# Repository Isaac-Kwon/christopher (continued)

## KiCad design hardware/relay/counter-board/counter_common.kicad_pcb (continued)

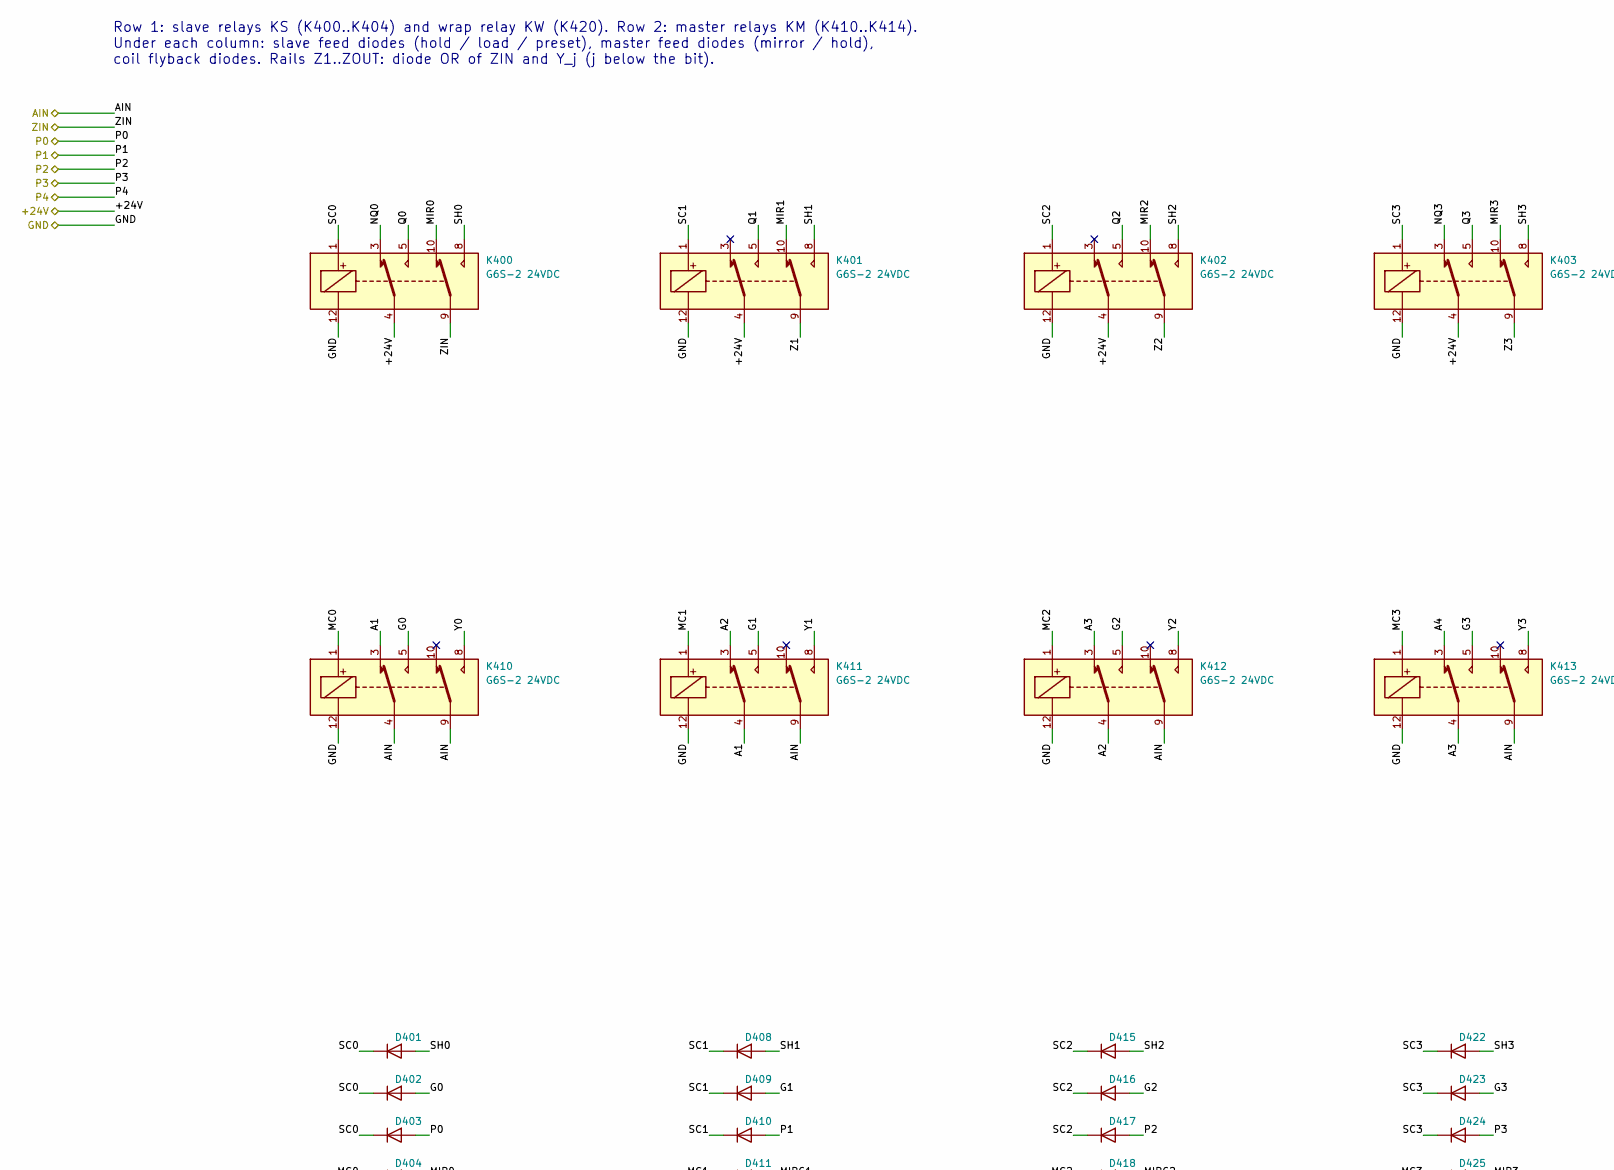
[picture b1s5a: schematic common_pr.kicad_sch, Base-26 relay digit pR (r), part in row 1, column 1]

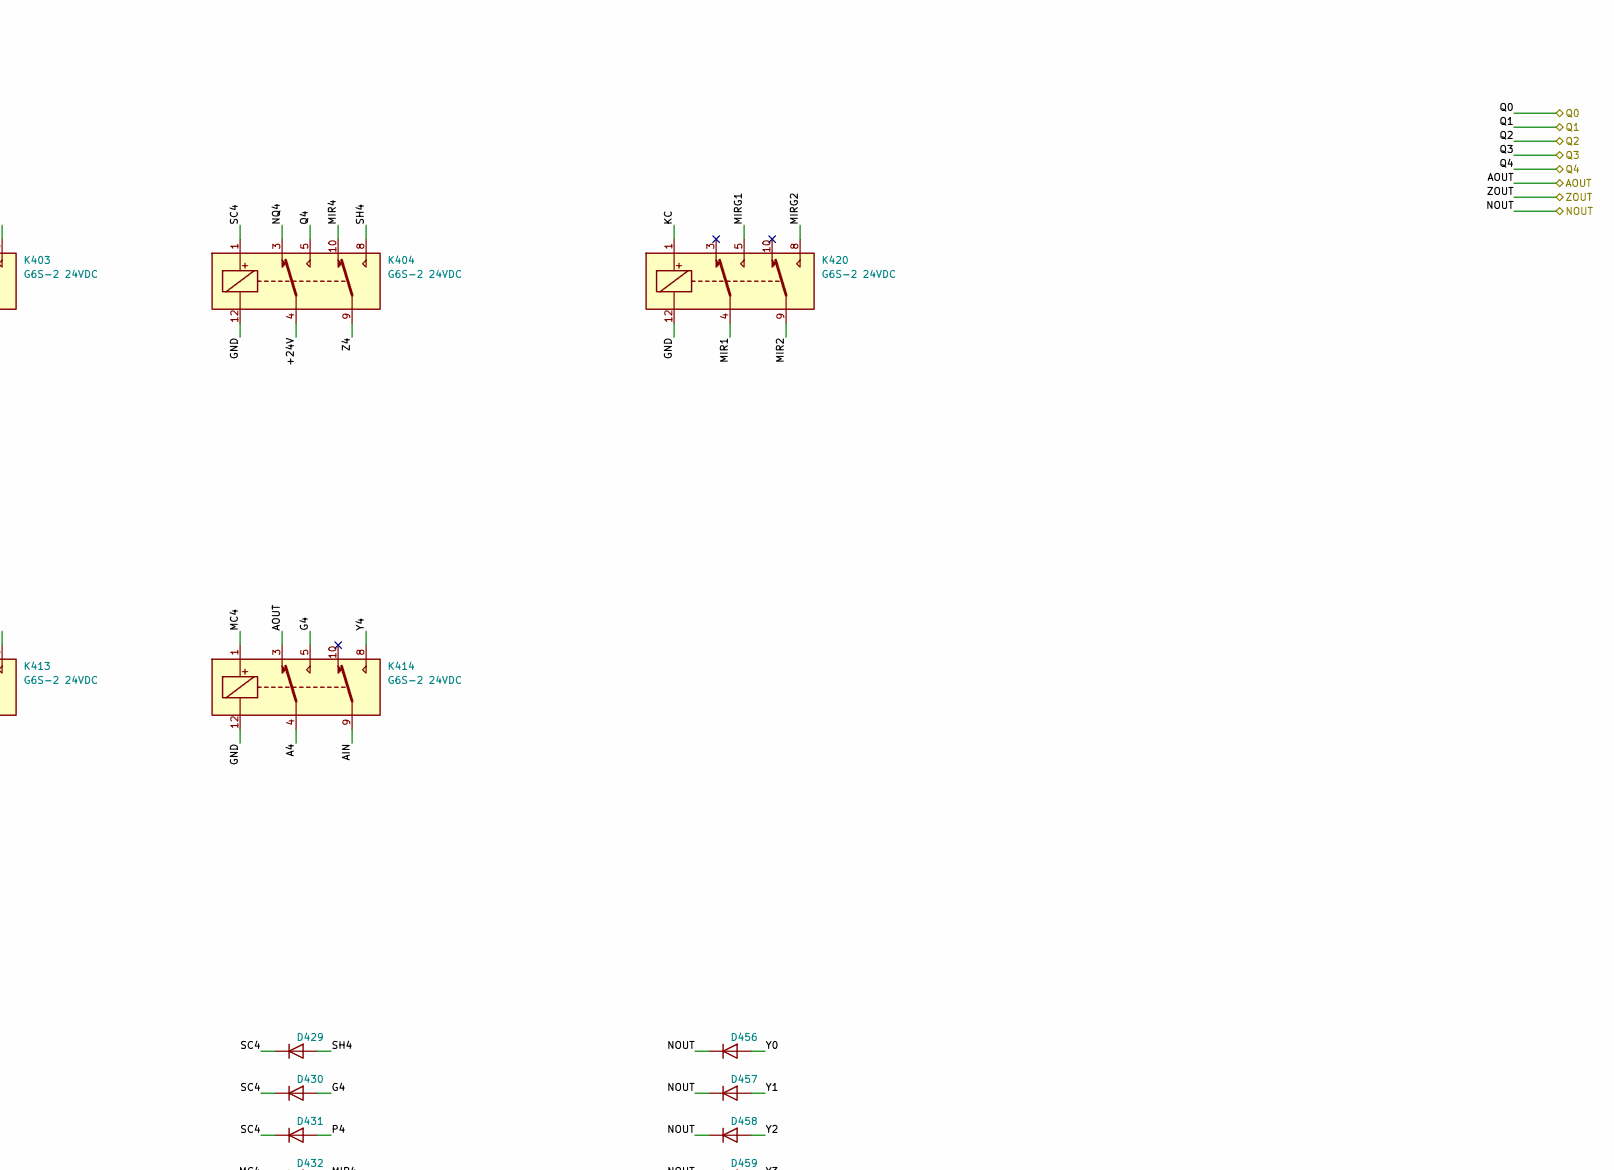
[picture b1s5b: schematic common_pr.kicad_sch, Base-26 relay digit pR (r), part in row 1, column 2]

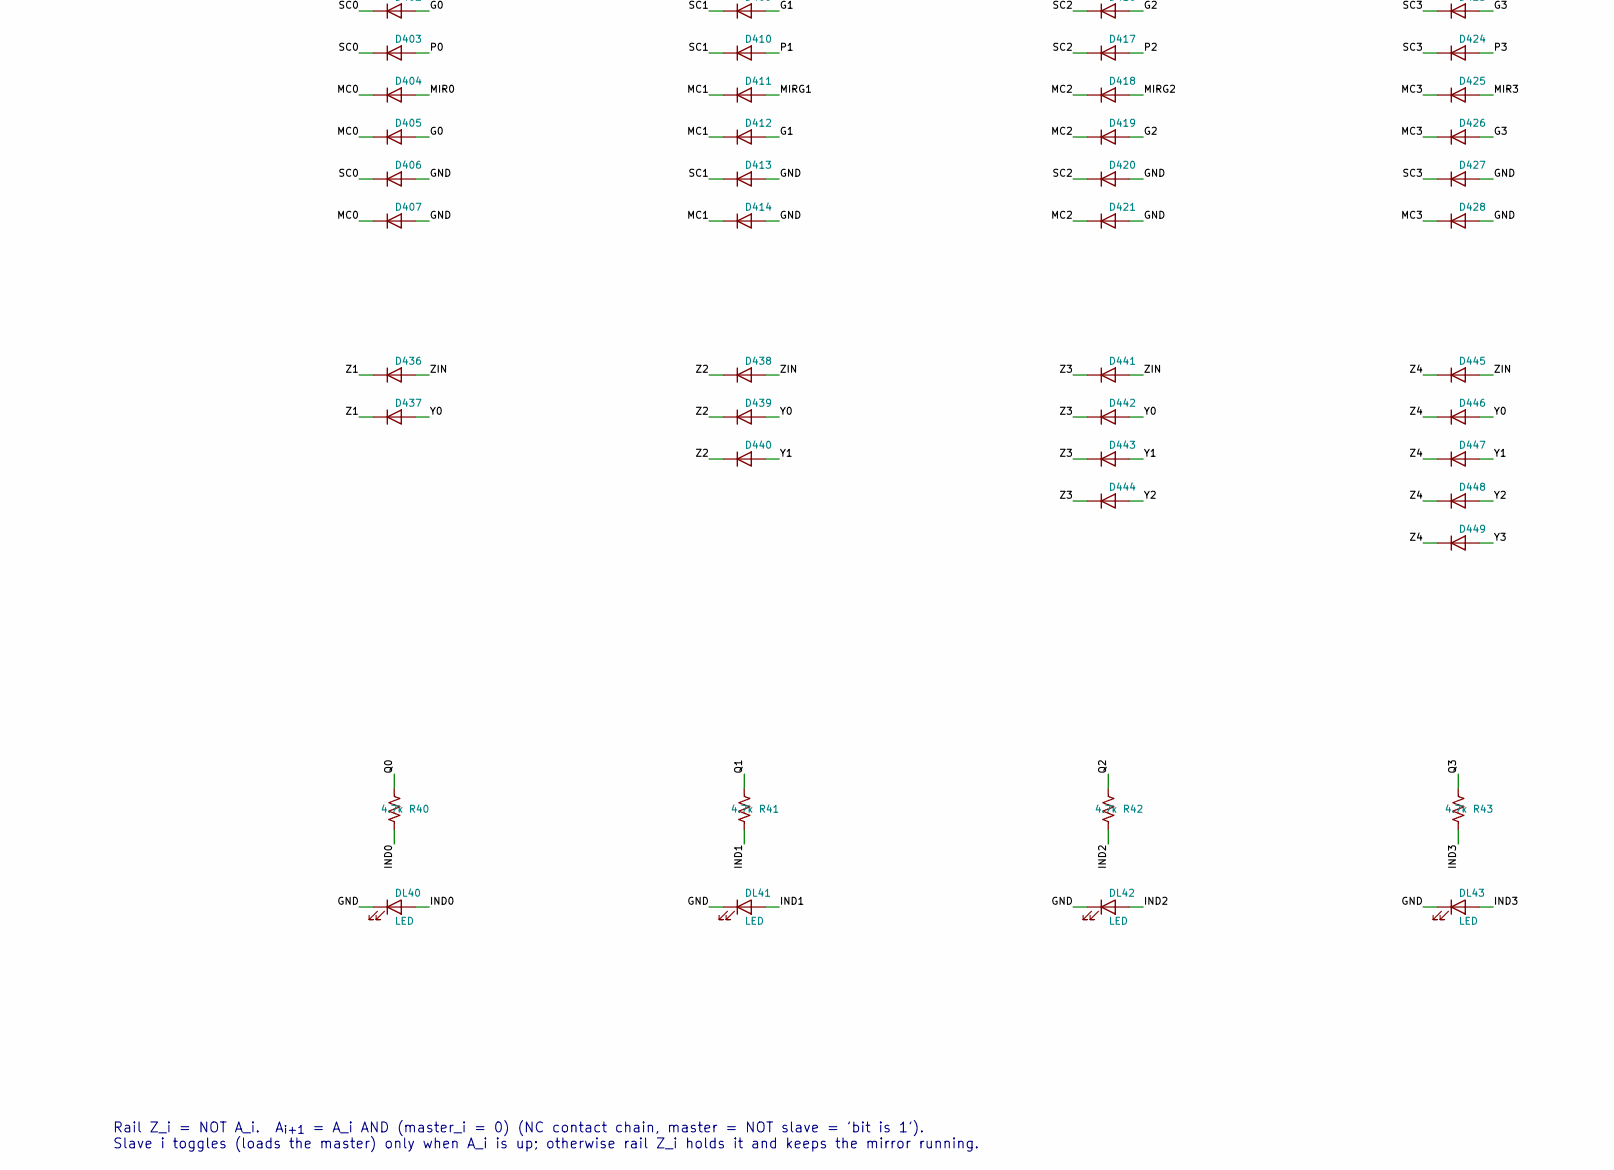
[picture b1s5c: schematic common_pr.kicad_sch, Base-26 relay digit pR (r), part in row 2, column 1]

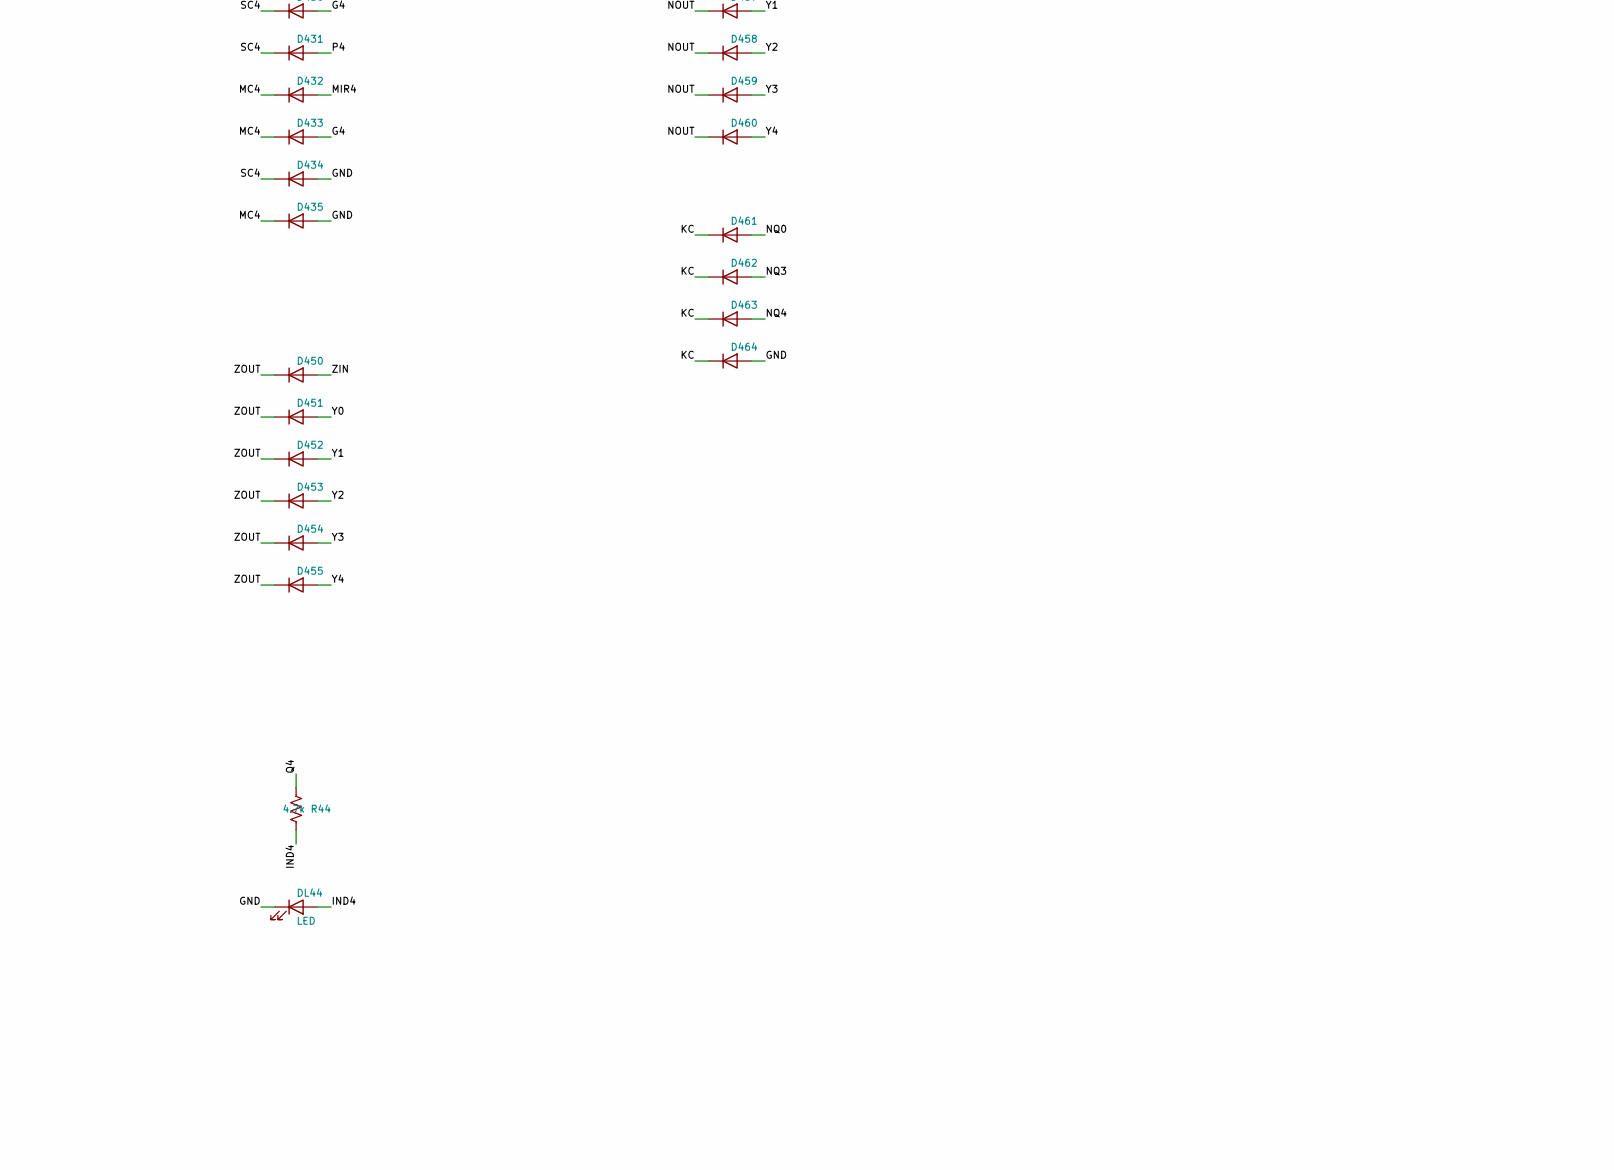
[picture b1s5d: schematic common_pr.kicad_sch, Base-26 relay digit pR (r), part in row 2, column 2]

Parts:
D401, D402, D403, D404, D405, D408, D409, D410, D411, D412, D415, D416, D417, D418, D419, D422, D423, D424, D425, D426, D429, D430, D431, D432, D433, D436, D437, D438, D439, D440, D441, D442, D443, D444, D445, D446, D447, D448, D449, D450, D451, D452, D453, D454, D455, D456, D457, D458, D459, D460, D461, D462, D463: 1N5819W; D_SOD-123
D406, D407, D413, D414, D420, D421, D427, D428, D434, D435, D464: 1N4148W; D_SOD-123
DL40, DL41, DL42, DL43, DL44: LED; LED_0603_1608Metric
K400, K401, K402, K403, K404, K410, K411, K412, K413, K414, K420: G6S-2 24VDC; Relay_DPDT_Omron_G6S-2
R40, R41, R42, R43, R44: 4.7k; R_0603_1608Metric

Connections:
/+24V: K400.4, K401.4, K402.4, K403.4, K404.4; also elsewhere on the board
/A1B: K410.4, K410.9, K411.9, K412.9, K413.9, K414.9; also elsewhere on the board
/DIGIT_PR/A1: K410.3, K411.4
/DIGIT_PR/A2: K411.3, K412.4
/DIGIT_PR/A3: K412.3, K413.4
/DIGIT_PR/A4: K413.3, K414.4
/DIGIT_PR/AOUT: K414.3
/DIGIT_PR/G0: D402.2 (A), D405.2 (A), K410.5
/DIGIT_PR/G1: D409.2 (A), D412.2 (A), K411.5
/DIGIT_PR/G2: D416.2 (A), D419.2 (A), K412.5
/DIGIT_PR/G3: D423.2 (A), D426.2 (A), K413.5
/DIGIT_PR/G4: D430.2 (A), D433.2 (A), K414.5
/DIGIT_PR/IND0: DL40.2 (A), R40.2
/DIGIT_PR/IND1: DL41.2 (A), R41.2
/DIGIT_PR/IND2: DL42.2 (A), R42.2
/DIGIT_PR/IND3: DL43.2 (A), R43.2
/DIGIT_PR/IND4: DL44.2 (A), R44.2
/DIGIT_PR/KC: D461.1 (K), D462.1 (K), D463.1 (K), D464.1 (K), K420.1
/DIGIT_PR/MC0: D404.1 (K), D405.1 (K), D407.1 (K), K410.1
/DIGIT_PR/MC1: D411.1 (K), D412.1 (K), D414.1 (K), K411.1
/DIGIT_PR/MC2: D418.1 (K), D419.1 (K), D421.1 (K), K412.1
/DIGIT_PR/MC3: D425.1 (K), D426.1 (K), D428.1 (K), K413.1
/DIGIT_PR/MC4: D432.1 (K), D433.1 (K), D435.1 (K), K414.1
/DIGIT_PR/MIR0: D404.2 (A), K400.10
/DIGIT_PR/MIR1: K401.10, K420.4
/DIGIT_PR/MIR2: K402.10, K420.9
/DIGIT_PR/MIR3: D425.2 (A), K403.10
/DIGIT_PR/MIR4: D432.2 (A), K404.10
/DIGIT_PR/MIRG1: D411.2 (A), K420.5
/DIGIT_PR/MIRG2: D418.2 (A), K420.8
/DIGIT_PR/NOUT: D456.1 (K), D457.1 (K), D458.1 (K), D459.1 (K), D460.1 (K)
/DIGIT_PR/NQ0: D461.2 (A), K400.3
/DIGIT_PR/NQ3: D462.2 (A), K403.3
/DIGIT_PR/NQ4: D463.2 (A), K404.3
/DIGIT_PR/SC0: D401.1 (K), D402.1 (K), D403.1 (K), D406.1 (K), K400.1
/DIGIT_PR/SC1: D408.1 (K), D409.1 (K), D410.1 (K), D413.1 (K), K401.1
/DIGIT_PR/SC2: D415.1 (K), D416.1 (K), D417.1 (K), D420.1 (K), K402.1
/DIGIT_PR/SC3: D422.1 (K), D423.1 (K), D424.1 (K), D427.1 (K), K403.1
/DIGIT_PR/SC4: D429.1 (K), D430.1 (K), D431.1 (K), D434.1 (K), K404.1
/DIGIT_PR/SH0: D401.2 (A), K400.8
/DIGIT_PR/SH1: D408.2 (A), K401.8
/DIGIT_PR/SH2: D415.2 (A), K402.8
/DIGIT_PR/SH3: D422.2 (A), K403.8
/DIGIT_PR/SH4: D429.2 (A), K404.8
/DIGIT_PR/Y0: D437.2 (A), D439.2 (A), D442.2 (A), D446.2 (A), D451.2 (A), D456.2 (A), K410.8
/DIGIT_PR/Y1: D440.2 (A), D443.2 (A), D447.2 (A), D452.2 (A), D457.2 (A), K411.8
/DIGIT_PR/Y2: D444.2 (A), D448.2 (A), D453.2 (A), D458.2 (A), K412.8
/DIGIT_PR/Y3: D449.2 (A), D454.2 (A), D459.2 (A), K413.8
/DIGIT_PR/Y4: D455.2 (A), D460.2 (A), K414.8
/DIGIT_PR/Z1: D436.1 (K), D437.1 (K), K401.9
/DIGIT_PR/Z2: D438.1 (K), D439.1 (K), D440.1 (K), K402.9
/DIGIT_PR/Z3: D441.1 (K), D442.1 (K), D443.1 (K), D444.1 (K), K403.9
/DIGIT_PR/Z4: D445.1 (K), D446.1 (K), D447.1 (K), D448.1 (K), D449.1 (K), K404.9
/DIGIT_PR/ZOUT: D450.1 (K), D451.1 (K), D452.1 (K), D453.1 (K), D454.1 (K), D455.1 (K)
/GND: D403.2 (A), D406.2 (A), D407.2 (A), D410.2 (A), D413.2 (A), D414.2 (A), D417.2 (A), D420.2 (A), D421.2 (A), D424.2 (A), D427.2 (A), D428.2 (A), D431.2 (A), D434.2 (A), D435.2 (A), D464.2 (A), DL40.1 (K), DL41.1 (K), DL42.1 (K), DL43.1 (K), DL44.1 (K), K400.12, K401.12, K402.12, K403.12, K404.12, K410.12, K411.12, K412.12, K413.12, K414.12, K420.12; also elsewhere on the board
/R0: K400.5, R40.1; also elsewhere on the board
/R1: K401.5, R41.1; also elsewhere on the board
/R2: K402.5, R42.1; also elsewhere on the board
/R3: K403.5, R43.1; also elsewhere on the board
/R4: K404.5, R44.1; also elsewhere on the board
/Z1B: D436.2 (A), D438.2 (A), D441.2 (A), D445.2 (A), D450.2 (A), K400.9; also elsewhere on the board

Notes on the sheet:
Row 1: slave relays KS (K400..K404) and wrap relay KW (K420). Row 2: master relays KM (K410..K414). Under each column: slave feed diodes (hold / load / preset), master feed diodes (mirror / hold), coil flyback diodes. Rails Z1..ZOUT: diode OR of ZIN and Y_j (j below the bit).
Rail Z_i = NOT A_i. A_{i+1} = A_i AND (master_i = 0) (NC contact chain, master = NOT slave = 'bit is 1'). Slave i toggles (loads the master) only when A_i is up; otherwise rail Z_i holds it and keeps the mirror running.

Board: 4 copper layers, 391 parts (0 on the bottom side), 264 nets, no tracks yet.

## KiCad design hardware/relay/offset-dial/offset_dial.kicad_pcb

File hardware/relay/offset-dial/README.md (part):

# 릴레이식 오프셋 다이얼과 다이얼 띠 (모듈 N, 회로도 + 기판 배치 + 기구 치수)

작성일: 2026-11-16 · 상태: **코드 트랙 회전 스위치(고정자 기판) 생성, ERC 0건, 기판 동박 형상 × 회전자 모델 × 계수기 유닛 보드 넷리스트로 26위치 전부 검증(허용 오차 모서리, break-before-make 훑기, 시스템 구동), 음성 시험 8/8(+ 기판 3/3), 기판 배치(미배선) DRC 0건, 배선은 사용자가. 기구(회전자·멈춤·손잡이)는 치수로만.** · 관련: `hardware/relay/layout.md` 3.5절(다이얼 띠), 5절 4번, `hardware/relay/concept.md` 5.2절, `hardware/relay/counter-board/README.md` 3·5절(유닛 J2 `DIAL`), `docs/decisions/0003-interfaces.md` 5.1–5.2절, `hardware/common/power-unit.md` 4절(전원 리셋 버튼), 기준 모델 `crates/christopher-core/src/relay.rs`(`Counters`), 메뉴 카드 `hardware/common/menu-cards/*.json`(`drum_offset_letters`)

**표기.** **(계산)** = 이 문서의 산술, **(추정)** = 실측·시제품 전 값, **(미확인)** = 데이터시트로 확인하지 못한 것. 단위는 mm, 각도는 관람객 쪽에서 본 시계 방향(12시 = 0°).

## 1. 무엇인가

유닛마다 하나씩 있는 **26위치 회전 스위치**다. 관람객(또는 운영자)이 메뉴 카드의 크립 오프셋 글자(`drum_offset_letters`의 셋째 글자, k = 글자 − A)에 손잡이를 맞추면, `HOME` 때 그 유닛의 계수기 유닛 보드가 a1 = k, a2 = −k mod 26을 프리셋으로 받는다(`counter-board/README.md` 3절, `relay.rs` `Counters::home`).

26위치 기성 회전 스위치는 찾지 못했다(`concept.md` 5.2절). 그래서 **기판 자체가 고정자**인 코드 트랙 스위치를 만들었다.

| 부분 | 내용 | 이 디렉터리에서 |
|---|---|---|
| 고정자 | 116 × 58 기판 한 장(2층). 회전자 쪽(F)에 동심 링 11개(COM + a1·a2 각 5비트), 관람객 쪽(B)에 글자 눈금 A–Z | 회로도·기판 배치(생성), 형상 검증 |
| 회전자 | 와이퍼 빗(끝 11개, 한 도체 = COM 다리), 허브 | 치수(4절, `dialmech.py`) |
| 멈춤 | 26홈 멈춤 원판 + 볼 플런저 | 치수(4절) |
| 손잡이·축·받침 | Ø40 손잡이, Ø6 축, 앞 부싱, 뒤 받침판 | 치수(4절) |
| 다이얼 띠 | 같은 다이얼 기판 12장 + 앞판 + 조작 장치 넷(속도 선택, 한 걸음, 전원 리셋, 전원 표시등) | 5절 (조작 장치는 패널 부품 + 배선표) |

파일: 생성기 `gen_dial.py`(회로도, 프로젝트 심볼 라이브러리 `christopher_dial.kicad_sym`, 풋프린트 `christopher_dial.pretty/OffsetDial26_CodeTracks.kicad_mod`, `sym-lib-table`, `fp-lib-table`), `gen_dial_pcb.py`(배치), 기구 수치 `dialmech.py`, 검증기 `verify_dial.py`(형상 × 회전자 × 계수기), `verify_dial_pcb.py`(기판). 공통 도우미는 `../position-display/kigen.py`. 생성물을 손으로 고치지 말고 생성기를 고친다.

## 2. 코드

### 2.1 계수기가 기대하는 것

계수기 유닛 보드 J2 `DIAL`(D-sub 15 수): 1 `DIAL_COM`(= `LOAD`), 2–6 a1 코드 비트 0–4, 7–11 a2 코드 비트 0–4, 12–13 0 V, 14–15 예약. **다이얼은 COM을 1인 비트의 핀에 잇는다**(`counter-board/README.md` 5절). `LOAD`가 24 V인 동안(`HOME`의 Q3–Q6, 약 25 ms, 관찰 모드에서는 약 108 ms) 이은 핀이 슬레이브 코일을 프리셋한다. 이 보드는 그 계약을 그대로 따르므로 **계수기 보드는 고치지 않았다.**

### 2.2 같은 출처에서 만든 코드

코드 표는 손으로 쓰지 않았다. `gen_dial.py`가 계수기 검증기의 기준 모델(`counter-board/verify_counter.py`의 `Counters`, `relay.rs`의 Python 이식)을 불러 위치 k마다 `Counters(k).controls()`의 (a1, a2)를 받아 링의 동박을 그린다.

| 글자 | A | B | C | D | E | F | G | H | I | J | K | L | M | N | O | P | Q | R | S | T | U | V | W | X | Y | Z |
|---|---|---|---|---|---|---|---|---|---|---|---|---|---|---|---|---|---|---|---|---|---|---|---|---|---|---|
| a1 = k | 0 | 1 | 2 | 3 | 4 | 5 | 6 | 7 | 8 | 9 | 10 | 11 | 12 | 13 | 14 | 15 | 16 | 17 | 18 | 19 | 20 | 21 | 22 | 23 | 24 | 25 |
| a2 = −k | 0 | 25 | 24 | 23 | 22 | 21 | 20 | 19 | 18 | 17 | 16 | 15 | 14 | 13 | 12 | 11 | 10 | 9 | 8 | 7 | 6 | 5 | 4 | 3 | 2 | 1 |

### 2.3 링과 호

| 링 j (안 → 밖) | 0 | 1 | 2 | 3 | 4 | 5 | 6 | 7 | 8 | 9 | 10 |
|---|---|---|---|---|---|---|---|---|---|---|---|
| 신호 (J1 핀) | COM (1) | a1 b4 (6) | a2 b4 (11) | a1 b3 (5) | a2 b3 (10) | a1 b2 (4) | a2 b2 (9) | a1 b1 (3) | a2 b1 (8) | a1 b0 (2) | a2 b0 (7) |
| 반지름 (중심선) | 9.0 | 10.7 | 12.4 | 14.1 | 15.8 | 17.5 | 19.2 | 20.9 | 22.6 | 24.3 | 26.0 |

- 링 폭 1.2, 링 사이 0.5. 바뀜이 잦은 아래 비트를 바깥 링에 두어 호가 길다.
- 링 0(COM)은 끊김 없는 고리다. 코드 링은 멈춤 위치 사이의 **가운데 각((p ± ½) × 13.846°)**에서 잘리고, 같은 값이 이어지는 위치끼리는 한 호로 붙는다. 1인 구간의 호는 그 링의 넷(J1 핀), 0인 구간의 호는 **어디에도 잇지 않은 섬**(dummy)이다. 섬 덕분에 끝이 늘 같은 높이의 동박 위를 달린다(35 µm 턱은 0.5 mm 틈에만 있다).
- 호와 호 사이의 틈 0.5 mm(선 길이로 일정).
- 호는 생성된 풋프린트의 **패드**다(같은 링의 패드는 같은 번호 = 같은 넷). 호를 커넥터까지 잇는 것은 배선이므로 사용자가 한다(래츠네스트 56개). 접점 면은 경질 금도금(최소 ENIG)으로 하고 링 띠(r 8.2–26.8)의 솔더 마스크를 연다.

## 3. 왜 이렇게 해도 되는가 (break-before-make, 멈춤)

**빗 하나가 COM이다.** 회전자의 끝 11개는 한 도체다. 그래서 두 출력이 서로 이어지는 일은 COM을 거쳐서만 일어나고, COM에 이어진 핀은 모두 `LOAD` 전위라 "다른 위치의 접점끼리 붙는" 고전적 의미의 겹침(make-before-break)이 생길 곳이 없다. 남는 질문은 둘이다.

1. **멈춤 사이에서 읽히는 코드.** 끝 j가 위치 p와 p+1 사이에 있으면 그 비트는 p의 값, p+1의 값, 또는 (틈 위라서) 0이다. 어느 이웃에서도 0인 비트가 1이 될 수는 없다: 그런 호는 반 칸(6.9°) 넘어서야 시작한다. 따라서 **훑는 동안의 코드는 비트마다 두 이웃 코드의 합집합 안**이다(검증: 26구간 × 0.05° 간격 7,202점). 전환 중의 코드는 일반적으로 어느 글자의 코드도 아니지만(비트마다 따로 바뀐다), 그것이 계수기에 들어가는 것은 `LOAD`가 높은 25 ms(관찰 모드 약 108 ms)뿐이다.
2. **다이얼을 언제 읽는가.** `LOAD`는 `HOME` 중에만 높다(`sequencer/README.md` 3.2절). 운전 중에 다이얼을 돌려도 계수기는 바뀌지 않고 **다음 `HOME`에서야** 새 값을 받는다. `HOME`의 `LOAD` 창(25 ms, 관찰 모드 약 108 ms)에 손잡이를 돌리는 중이었다면 그 유닛의 프리셋이 틀릴 수 있으나 무해하다(코일 몇 개가 다이오드를 거쳐 먹을 뿐, 단락 없음). 다음 `HOME`으로 고친다. 전시 절차: **다이얼을 모두 맞춘 뒤 `HOME`**.

**멈춤 위치에서의 여유.** 멈춤에 놓인 회전자가 틀어질 수 있는 양(아래 표)보다 코드가 바뀌기 시작하는 각이 충분히 커야 한다.

| 원인 | 값 (추정) |
|---|---:|
| 멈춤 원판 홈의 가공 | ±0.2° |
| 원판–축 고정(지름 2 맞춤 핀) | ±0.3° |
| 허브–축(D컷) | ±0.5° |
| 빗 끝선–허브 | ±0.5° |
| 볼 플런저의 안착(스프링 놀이, 마찰) | ±0.5° |
| 고정자 구멍 위치·축 편심 0.2 mm (가장 안쪽 링 r = 10.7에서) | ±1.1° |
| **설계 허용** | **±3.0°**, 반지름 방향 ±0.3 mm |

검증 결과: 코드가 처음 바뀌는 회전자 오차는 **6.6°**(멈춤 간격 13.85°의 절반 6.92°에서 끝의 반지름과 틈을 뺀 값), 반지름 방향은 **0.75 mm**다. 설계 허용의 두 배 이상이다.

## 4. 기구 (치수, CAD 없음)

앞에서 뒤로: 손잡이 → 앞판 → 고정자 기판(B면이 앞) → 회전자 → 멈춤 원판 → 뒤 받침판.

| 부품 | 치수와 재료 | 비고 |
|---|---|---|
| 손잡이 | Ø40 × 16, 알루미늄(검정 아노다이징) 또는 POM. 치마에 지시선(흰색 메움), 고정 나사 M4로 축의 D컷에 | 지시선 = 빗 끝선. 조립 때 A에 맞춘다 |
| 축 | Ø6 h8 스테인리스, 길이 48. 앞 끝 D컷(깊이 0.5, 길이 12), 뒤에 E링 홈, 멈춤 원판용 Ø2 핀 구멍 | |
| 앞 부싱 | 황동 판 부싱 M10 × 0.75, 길이 9.5, 구멍 Ø6. 앞판에 너트로 고정 | 고정자의 가운데 구멍 Ø10.2(NPTH)를 지난다. 고정자는 부싱이 아니라 기둥이 잡는다 |
| 앞판 | 다이얼 띠의 알루미늄 2t. 다이얼마다 창 Ø58(글자 눈금이 보인다) | 5절 |
| 고정자 | 이 기판 116 × 58 × 1.6, 2층. M3 기둥 6 mm로 앞판 뒤에 | 글자 눈금 r = 24(높이 2.6), 눈금선 r = 20.6–21.8. 손잡이 치마(r = 20) 바깥 |
| 회전자 허브 | POM, Ø20 × 6, D구멍, 고정 나사 M3 | 빗을 리벳 2개로 |
| 와이퍼 빗 | 베릴륨 동(C17200) 0.15t, 경질 금도금 끝. 팔(폭 3, r 7–27) + 손가락 11개(폭 1.0)가 고정자 쪽으로 굽고 끝에 반구 딤플 Ø0.6 | **끝 반지름 9.0 + 1.7 j**(j = 0–10)가 한 반지름 선 위(±0.1). 손가락당 접촉력 0.3–0.5 N(처짐 0.4) |
| 멈춤 원판 | 강 Ø30 × 3, 26홈(V 90°, 깊이 0.8), 축에 Ø2 핀 | 홈 0이 빗 끝선과 같은 각 |
| 볼 플런저 | M6, 볼 Ø3, 끝 힘 6–8 N, 반지름 방향 | 멈춤 토크 최대 약 0.1 N·m **(계산: 7 N × 15 mm × tan 45°)** |
| 뒤 받침판 | 알루미늄 2t, 112 × 50, M3 기둥 14 mm로 고정자의 네 구멍에. J1 자리에 45 × 18 창 | 축 뒤 끝의 플랜지 미끄럼 베어링(청동 6 × 10 × 6), 플런저 보스 |
| 앞판 뒤 깊이 | 6 + 1.6 + 14 + 2 + 플런저 ≈ 30 | 다이얼 띠 뒤의 흡기 통로(`layout.md` 3.7절) 안 |

회전은 끝없이 돈다(Z 다음 A). k가 순환값이므로 멈춤 핀이 필요 없다. `dialmech.py`가 이 표의 수치(끝 반지름·접촉 반지름·허용 오차·멈춤 간격)를 가지고 있고, 생성기는 그 끝 아래에 링을 그리며 검증기는 그 수치로 회전자를 모사한다.

## 5. 다이얼 띠 (모듈 N)

`layout.md`는 "다이얼 띠 높이 60, 폭 1,800, 다이얼 12개(피치 120), 제어 칸 아래에 속도 선택·한 걸음 버튼·전원 리셋 버튼·전원 표시등"을 둔다. **기판 한 장으로 만들지 않았다**(1,800 mm 기판은 만들 수 없고, 유닛이 6개뿐인 기계에서는 다이얼도 6개면 된다).

- **다이얼 12개 = 같은 다이얼 기판 12장**(이 보드, 116 × 58). 띠의 앞판(알루미늄 2t, 1,800 × 60)에 피치 120으로 창 Ø58과 부싱 구멍을 내고 각 기판을 M3 기둥 넷으로 단다. 다이얼 n은 유닛 n의 바로 아래 열에 온다(`layout.md` 3.5절: c번 열의 아래 단 = 2c − 1, 위 단 = 2c → 열마다 다이얼 둘). 각 기판의 J1 → 그 유닛의 계수기 유닛 보드 J2: **D-sub 15 소켓–소켓 1:1 리본 0.3–0.7 m**(0003 5.1절). 기판 뒷면의 `UNIT` 칸에 유닛 번호를 적는다.
- **조작 장치 넷 = 22 mm 패널 부품**(제어 칸 아래 360 구간). 관람객이 누르는 것이므로 산업용 22 mm 부품(IP65, 금속 테)으로 하고 기판에 올리지 않는다. 전원 리셋 버튼은 전원부의 안전 회로(K_E 리셋, `power-unit.md` 4.1절)에 직접 들어가야 하므로 다른 기판을 거치지 않는다.

| 장치 | 부품 | 잇는 곳 | 상태 |
|---|---|---|---|
| S_R 전원 리셋 | 22 mm 누름 버튼, 파랑, 1a | 전원부 단자대: K_E 리셋 회로(KM1·KM2 b 보조 접점과 직렬), 0.5 mm² 두 가닥 | `power-unit.md` 4.1절 그대로 |
| H_SW 전원 표시등 | 22 mm LED 표시등 24 V DC, 녹색(약 10 mA) | `+24V_SW` 모선 → 전원부 퓨즈 F39 0.5 A(새로) → 표시등 → 0 V | `power-unit.md` 3·6절에 F39를 더했다 |
| S_SPD 속도 선택 | 22 mm 2위치 선택 스위치(빠름 / 관찰), 1a(**관찰에서 닫힘**) | 순서기 J10 `PANEL`: 1번(`+24V_SW` 공급) – 접점 – 2번(`SPEED_OBS`) | `sequencer/README.md` 2.1절 |
| S_STP 한 걸음 | 22 mm 누름 버튼(순간), 검정, 1a | 순서기 J10 `PANEL`: 1번 – 접점 – 3번(`STEP`) | `sequencer/README.md` 3.3절 |

속도 선택과 한 걸음은 **순서기의 J10 `PANEL`**(5.08 mm 4극 나사 단자)로 간다(2026-11-16): 1 `+24V_SW` 스위치 공급(순서기 안의 자동 복귀 퓨즈 0.1 A), 2 `SPEED_OBS` 되돌림, 3 `STEP` 되돌림, 4 예비(미연결). 두 스위치의 공통 단자를 1번에 묶고 각 1a 접점의 다른 쪽을 2번·3번에 잇는다(0.5 mm² 세 가닥). 스위치 접점이 24 V 레벨 신호를 만들고 순서기의 입력은 0003 2.2절의 받는 쪽 규칙(직렬 쇼트키, 코일 쪽 클램프, 핀 쪽 풀다운 + LED, 약 12.6 mA)을 따른다. 처음 제안한 배치와 같다.

- **관찰 모드**: 순서기 555의 R2에 680 kΩ이 직렬로 들어가 틱 27 ms, **위치 주기 270 ms(초당 3.7 위치)**. 운전 중 언제 돌려도 주기가 끊기거나 `CK`가 두 번 나가지 않는다(저항만 바꾸므로 어떤 틱도 빠른 틱보다 짧아지지 않는다).
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
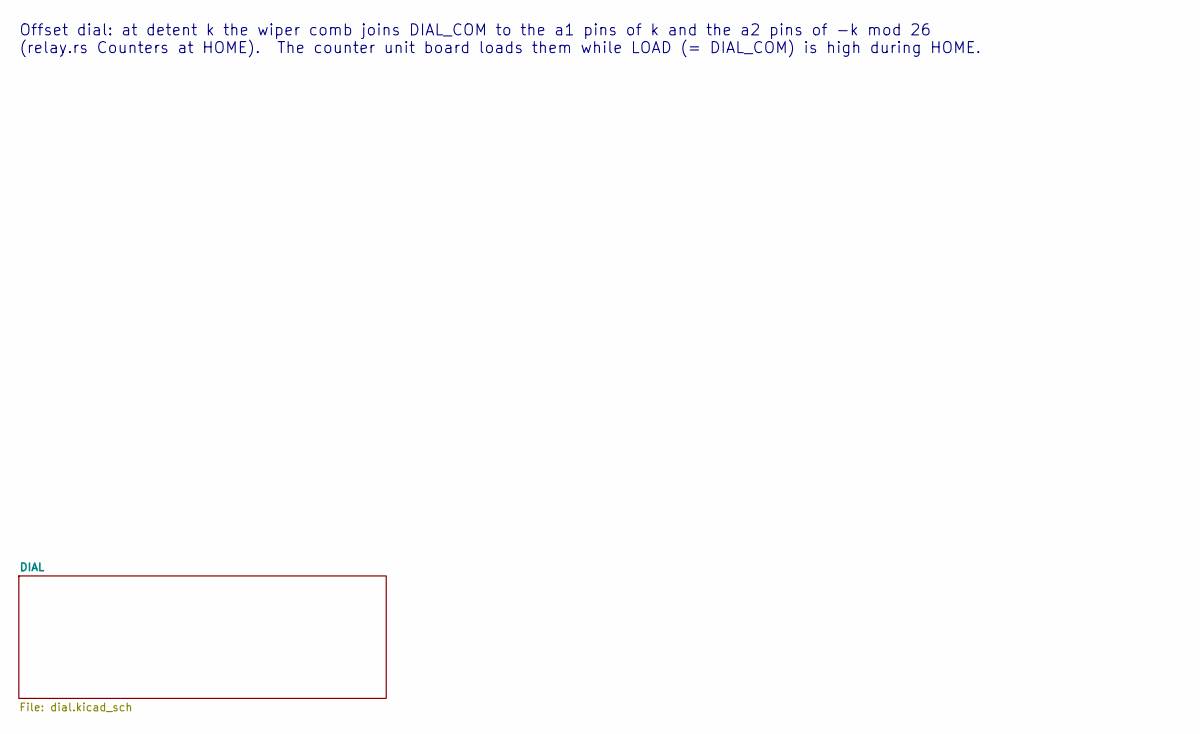
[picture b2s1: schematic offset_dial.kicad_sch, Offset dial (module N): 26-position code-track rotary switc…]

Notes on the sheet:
Offset dial: at detent k the wiper comb joins DIAL_COM to the a1 pins of k and the a2 pins of -k mod 26 (relay.rs Counters at HOME). The counter unit board loads them while LOAD (= DIAL_COM) is high during HOME.

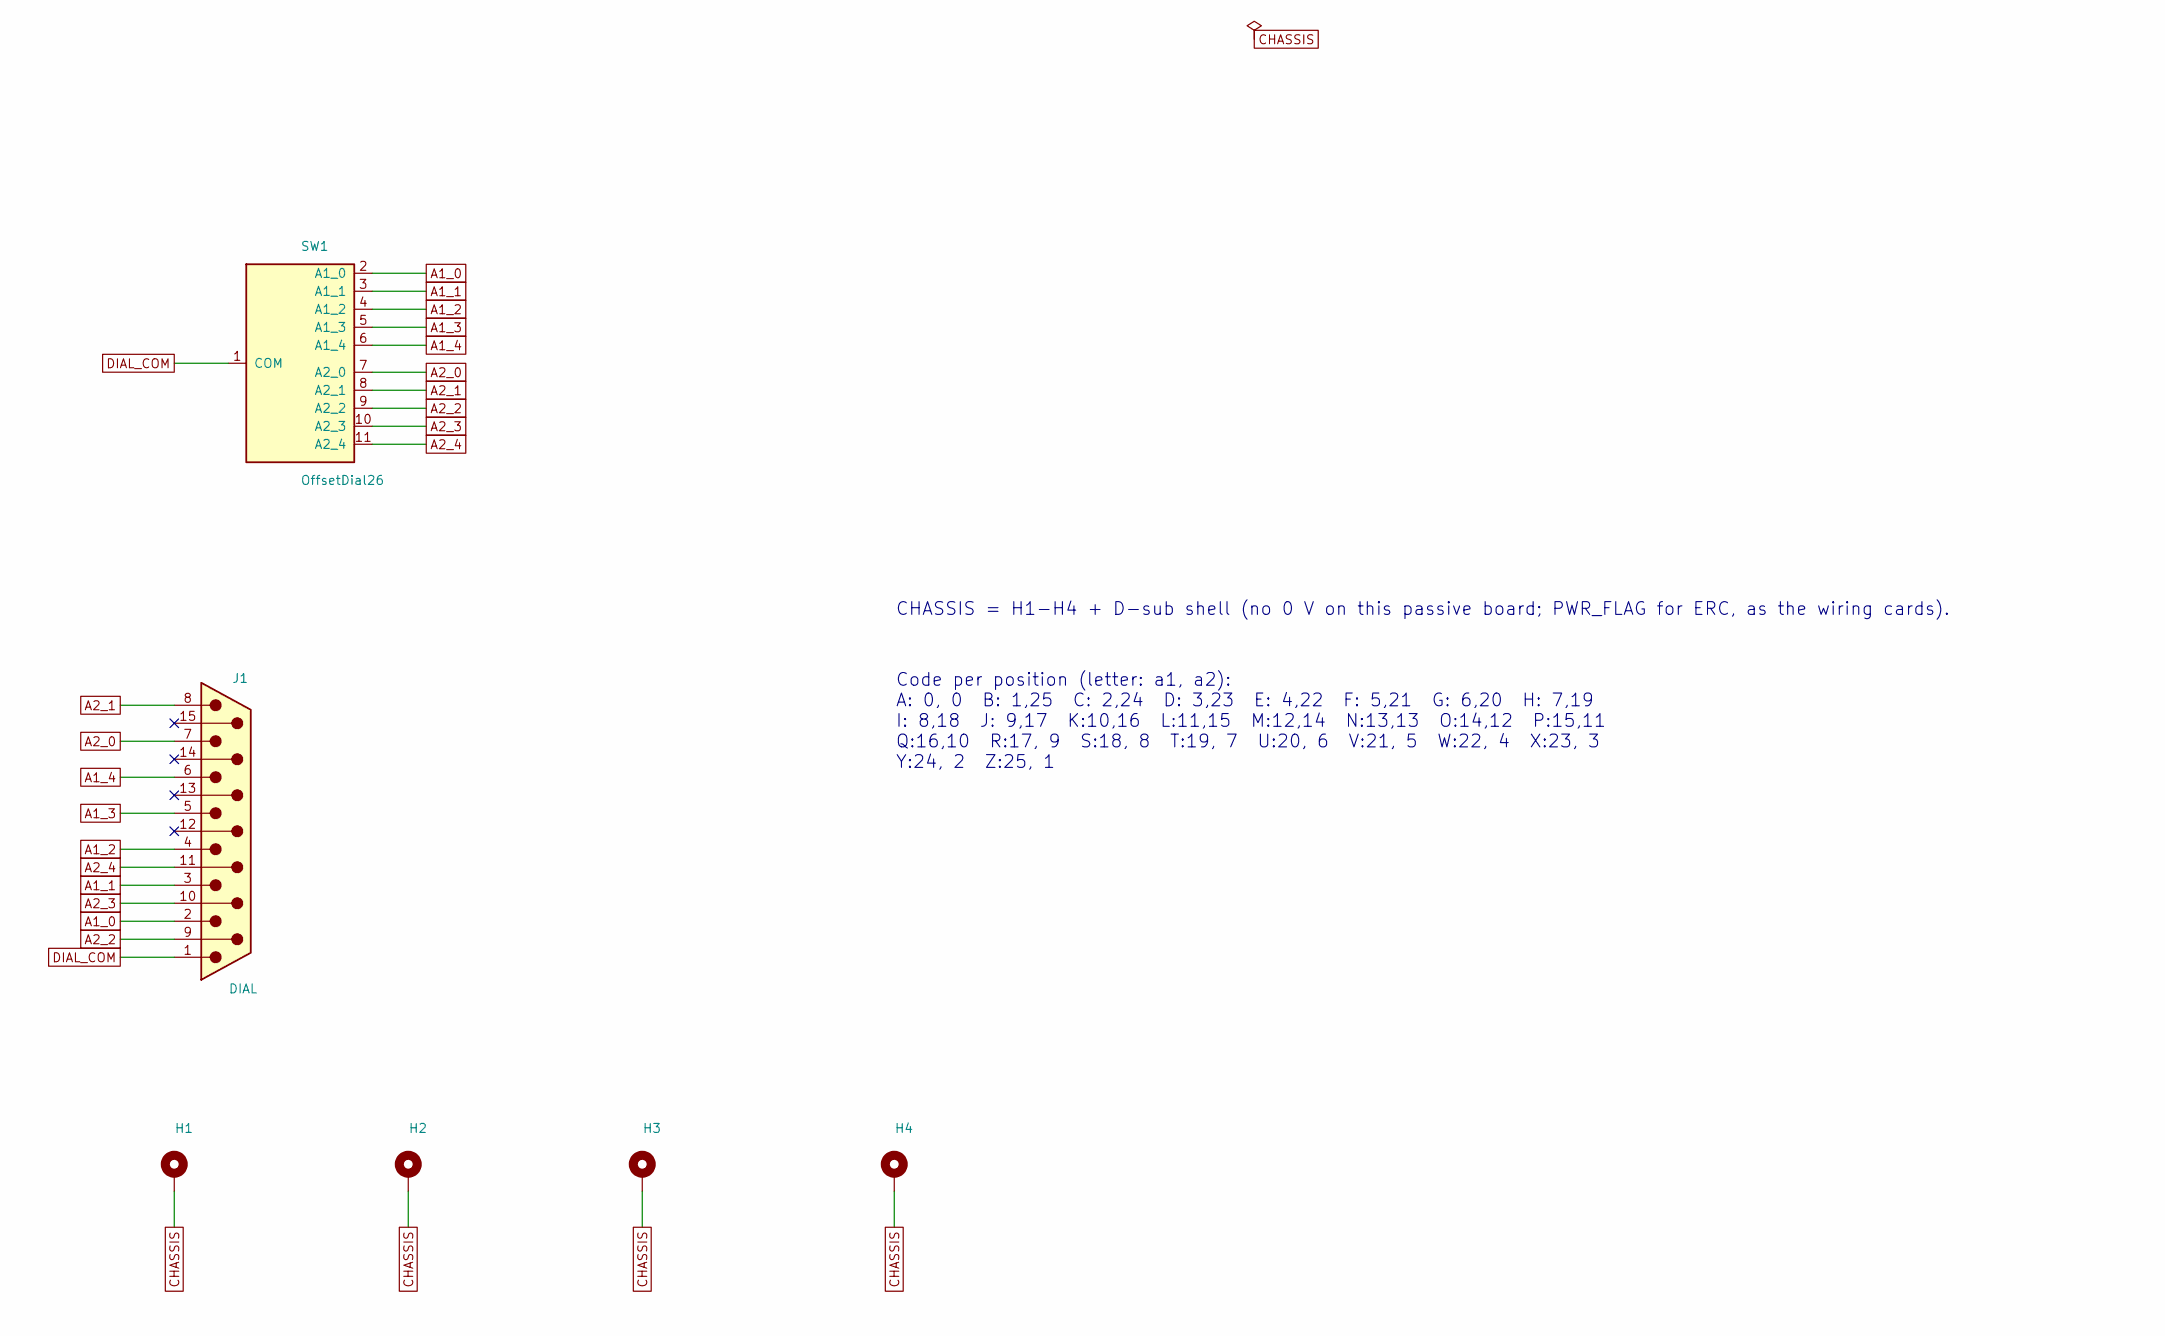
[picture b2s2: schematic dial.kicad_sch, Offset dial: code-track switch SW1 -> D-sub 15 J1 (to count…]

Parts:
H1, H2, H3, H4: MountingHole_Pad; MountingHole_3.2mm_M3_Pad
J1: DIAL; DSUB-15_Pins_Vertical_P2.77x2.84mm_MountingHoles
SW1: OffsetDial26; OffsetDial26_CodeTracks

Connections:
A1_0: J1.2, SW1.2 (A1_0)
A1_1: J1.3, SW1.3 (A1_1)
A1_2: J1.4, SW1.4 (A1_2)
A1_3: J1.5, SW1.5 (A1_3)
A1_4: J1.6, SW1.6 (A1_4)
A2_0: J1.7, SW1.7 (A2_0)
A2_1: J1.8, SW1.8 (A2_1)
A2_2: J1.9, SW1.9 (A2_2)
A2_3: J1.10, SW1.10 (A2_3)
A2_4: J1.11 (P111), SW1.11 (A2_4)
CHASSIS: H1.1, H2.1, H3.1, H4.1, J1.SH
DIAL_COM: J1.1, SW1.1 (COM)

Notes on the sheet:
Code per position (letter: a1, a2): A: 0, 0 B: 1,25 C: 2,24 D: 3,23 E: 4,22 F: 5,21 G: 6,20 H: 7,19 I: 8,18 J: 9,17 K:10,16 L:11,15 M:12,14 N:13,13 O:14,12 P:15,11 Q:16,10 R:17, 9 S:18, 8 T:19, 7 U:20, 6 V:21, 5 W:22, 4 X:23, 3 Y:24, 2 Z:25, 1
CHASSIS = H1-H4 + D-sub shell (no 0 V on this passive board; PWR_FLAG for ERC, as the wiring cards).

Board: 2 copper layers, 6 parts (0 on the bottom side), 12 nets, no tracks yet.

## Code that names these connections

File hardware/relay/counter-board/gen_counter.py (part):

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    root.pin_net(S_PTC, fx, y, "2", "VF")
    qx = g(x + 80.0)
    root.symbol(S_PMOS, qx, y, "Q1", "P-MOSFET (reverse polarity)", FP_PMOS, "", "Series P-channel MOSFET: D = supply side, S = board +24V; Vgs limited by DZ1", path)
    root.pin_net(S_PMOS, qx, y, "1", "GATE")
    root.pin_net(S_PMOS, qx, y, "2", "VF")
    root.pin_net(S_PMOS, qx, y, "3", "+24V")
    zx = g(x + 120.0)
    root.symbol(S_ZENER, zx, y, "DZ1", "12V", FP_DIODE, "", "Gate-source zener 12 V (anode on the gate)", path)
    root.pin_net(S_ZENER, zx, y, "1", "+24V")     # K
    root.pin_net(S_ZENER, zx, y, "2", "GATE")     # A
    gx = g(x + 160.0)
    root.symbol(S_R, gx, y, "RG1", "100k", FP_R, "", "Gate pull-down to 0 V", path)
    root.pin_net(S_R, gx, y, "1", "GATE")
    root.pin_net(S_R, gx, y, "2", "GND")
    tx = g(x + 200.0)
    root.symbol(S_TVS, tx, y, "TVS1", "SMAJ33A", FP_TVS, "", "TVS 33 V across the board supply (behind the MOSFET)", path)
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        hx, hy = g(x + 40.0 * k), g(y)
        root.symbol(S_HOLE, hx, hy, f"H{k + 1}", "MountingHole_Pad", FP_HOLE, "",
                    "Plated M3 mounting hole, net CHASSIS (metal standoff to the frame / PE)", path, show_value=False, in_bom=False)
        root.pin_net(S_HOLE, hx, hy, "1", "CHASSIS", 5.08)
    rx, ry = g(x + 180.0), g(y)
    root.symbol(S_R, rx, ry, "RCH1", "1M", FP_R, "", "CHASSIS to 0 V: static drain", path)
    root.pin_net(S_R, rx, ry, "1", "CHASSIS", 5.08)
    root.pin_net(S_R, rx, ry, "2", "GND", 5.08)
    cx, cy = g(x + 220.0), g(y)
    root.symbol(S_C, cx, cy, "CCH1", "10nF 100V", FP_C, "", "CHASSIS to 0 V: ESD / HF path", path)
    root.pin_net(S_C, cx, cy, "1", "CHASSIS", 5.08)
    root.pin_net(S_C, cx, cy, "2", "GND", 5.08)
    root.text("CHASSIS (decision 0003 7.1): D-sub shells (footprint pads SH, not in the symbols) and mounting holes H1-H4 = CHASSIS, "
              "not 0 V. RCH1 1 Mohm || CCH1 10 nF/100 V between CHASSIS and 0 V.", x, y + 14.0, 1.6)


# bus connector (identical pinout on both boards)
BUS_PINS = {1: "A2B", 2: "Z2B", 3: "A1B", 4: "Z1B",
            **{5 + b: f"L{b}" for b in range(BITS)}, **{10 + b: f"T{b}" for b in range(BITS)},
            15: "LOAD", 19: "GND", 20: "GND", 21: "GND"}   # 16-18 reserved (were +24 V; 0003 K2)
BUS_DESC = ("D-sub 25 pins: 1 A2B (a2 advance rail), 2 Z2B (a2 hold rail), 3 A1B, 4 Z1B (a1 rails), 5-9 L0..L4 (a4 = l code), "
            "10-14 T0..T4 (a3 code), 15 LOAD (HOME preset level), 16-18 reserved (no power on signal connectors), 19-21 0 V, 22-25 reserved")
# clock bus B (sequencer J4 CLK_B, units 7-12; 0003 K7): the rails and LOAD of bus B have their own nets, the code lines
# L/T and 0 V are shared with bus A
BUS_B = {"A2B": "A2B_B", "Z2B": "Z2B_B", "A1B": "A1B_B", "Z1B": "Z1B_B", "LOAD": "LOAD_B"}
BUS_PINS_B = {p: BUS_B.get(n, n) for p, n in BUS_PINS.items()}
CLOCK_DESC = ("D-sub 9 pins: 1 CK (+24 V during the commit phase), 2 NCK (+24 V otherwise; both 0 V = LOAD/clear state), "
              "3 LOAD, 4-5 reserved (no power on signal connectors), 6-7 0 V, 8-9 reserved")


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              {1: "CK_B", 2: "NCK_B", 3: "LOAD_B", 6: "GND", 7: "GND"},
              "Clock bus B (units 7-12), same pins as J1: " + CLOCK_DESC)
    connector(root, path0, S_DB25, "J6", "UNIT_BUS_B", 25, 100.0, 180.0, BUS_PINS_B,
              "Unit bus B (units 7-12), same pins as J2 with the bus-B rails A2B_B Z2B_B A1B_B Z1B_B and LOAD_B "
              "(fed only from J5); L/T code lines and 0 V shared with J2. " + BUS_DESC)
    # 0003 K3: POS connector = the core position (l, m, r) as three 5-bit binary digits (no k), 24 V level
    pos = {**{1 + b: f"L{b}" for b in range(BITS)}, **{6 + b: f"M{b}" for b in range(BITS)},
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    dial.update({2 + b: f"PA1_{b}" for b in range(BITS)})
    dial.update({7 + b: f"PA2_{b}" for b in range(BITS)})
    connector(root, path0, S_DA15, "J2", "DIAL", 15, 40.0, 220.0, dial,
              "D-sub 15 pins: 1 DIAL_COM (= LOAD level, to the offset dial common), 2-6 a1 preset code (bit0..4, = k), "
              "7-11 a2 preset code (= -k mod 26), 12-13 0 V, 14-15 reserved. Dial contacts join COM to the code pins of the 1 bits")
    for j, (ref, nm, pref) in enumerate((("J3", "CTRL_A1", "C1_"), ("J4", "CTRL_A2", "C2_"),
                                         ("J5", "CTRL_A3", "C3_"), ("J6", "CTRL_A4", "C4_"))):
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
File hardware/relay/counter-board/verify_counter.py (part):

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            name = find1(n, "name")[1]
            for x in find_all(n, "node"):
                self.node_net[(find1(x, "ref")[1], find1(x, "pin")[1])] = name
        # D-sub shells are footprint pads "SH" with no schematic pin: they belong to net CHASSIS (0003 7.1),
        # the net of the plated mounting holes.  Adding them here keeps netlist, simulation and PCB in step.
        ch = self.node_net.get(("H1", "1"))
        if ch is not None:
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
BUS_CONN = {"A": "J2", "B": "J6"}          # common-board unit bus of clock bus A (units 1-6) / B (units 7-12)
CLOCK_CONN = {"A": "J1", "B": "J5"}
RAIL_PINS = (1, 2, 3, 4, 15)               # A2B Z2B A1B Z1B LOAD: the per-bus pins of the unit bus


def bus_of(u: int) -> str:
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                wires.append(((t, "J2", "1"), (t, "J2", str(7 + b))))          # a2 = -k
    # the sequencer switches both clock buses from one coil (README 11): "CK" etc. drive both, "CK_A" / "CK_B" one bus
    drives = {}
    for name, pin in (("CK", "1"), ("NCK", "2"), ("LOAD", "3")):
        for b, j in CLOCK_CONN.items():
            drives[f"{name}_{b}"] = [("C", j, pin)]
        drives[name] = drives[f"{name}_A"] + drives[f"{name}_B"]
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        if not alone(net(("J5", p))):
            errs.append(f"common: CLOCK_B J5 reserved pin {p} is connected")
    if net(("J6", "15")) != net(("J5", "3")):
        errs.append("common: unit bus B J6 pin 15 is not LOAD_B (J5 pin 3)")
    bus_a = {net(("J2", str(p))) for p in RAIL_PINS} | {net(("J1", q)) for q in ("1", "2", "3")}
    for p in range(1, 26):
        a, b = net(("J2", str(p))), net(("J6", str(p)))
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
def bus_isolation_errors(common: Netlist, unit: Netlist, trials: int = 300, seed: int = 31) -> list[str]:
    """Current split of the two clock buses (0003 K7): for random relay states, what is reachable from one bus's
    CK/NCK/LOAD (and the board +24 V) must not include the clock or unit-bus rail pins of the other bus.  So the
    rail current of units 7-12 comes only through J5, and that of the common digits + units 1-6 only through J1."""
    s = build_system(common, unit, [0, 7, 25, 3])
    rng = random.Random(seed)
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    ("common pL wrap relay: swap NC/NO (K120 pins 3<->5)", "common", "K120", "3", "5"),
    ("common a3 slave hold diode bit 2 reversed (D315 pins 1<->2)", "common", "D315", "1", "2"),
    ("common a3 hold-rail OR diode from LC reversed (D802 pins 1<->2)", "common", "D802", "1", "2"),
    ("common bus: swap A1B/Z1B (J2 pins 3<->4)", "common", "J2", "3", "4"),
    ("common bus: swap A2B/A1B (J2 pins 1<->3)", "common", "J2", "1", "3"),
    ("unit dial: swap a2 preset bits 0/2 (J2 pins 7<->9)", "unit", "J2", "7", "9"),
    ("unit a1 master bit 2: swap NC/NO (K212 pins 3<->5)", "unit", "K212", "3", "5"),
    ("unit a1 wrap relay: swap NC/NO (K220 pins 3<->5)", "unit", "K220", "3", "5"),
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    ("common pR slave bit 1: swap NC/NO of Q pole (K401 pins 3<->5)", "common", "K401", "3", "5"),
    ("common pR master bit 0: swap NC/NO of carry pole (K410 pins 3<->5), seen when r first advances", "common", "K410", "3", "5"),
    # 0003 K7: clock bus B -> twin masters -> unit bus B (units on bus B are the odd-numbered simulated units)
    ("common unit bus B: swap A1B_B/Z1B_B (J6 pins 3<->4)", "common", "J6", "3", "4"),
    ("common clock bus B: swap CK_B/NCK_B (J5 pins 1<->2)", "common", "J5", "1", "2"),
    ("common pM twin master bit 1: swap NC/NO of the bus-B carry pole (K231 pins 3<->5)", "common", "K231", "3", "5"),
    ("common pL twin master bit 3: YB on the NC instead of the NO contact (K133 pins 8<->10)", "common", "K133", "8", "10"),
]
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    ("common power input: reversed P-MOSFET (Q1 pins 2<->3)", "common", lambda nl: swap_node(nl, "Q1", "2", "3")),
    ("unit power input: reversed P-MOSFET (Q1 pins 2<->3)", "unit", lambda nl: swap_node(nl, "Q1", "2", "3")),
    ("common power input: PTC bypassed (F1 pin 2 on the supply input)", "common", lambda nl: move_node(nl, ("F1", "2"), ("J3", "1"))),
    ("unit power input: gate zener reversed (DZ1 pins 1<->2)", "unit", lambda nl: swap_node(nl, "DZ1", "1", "2")),
    ("unit power input: TVS missing from the board +24V (TVS1 pin 2 moved to 0 V)", "unit", lambda nl: move_node(nl, ("TVS1", "2"), ("J7", "2"))),
    ("common: +24 V on the old clock pin J1.4 (power on a signal connector)", "common", lambda nl: move_node(nl, ("J1", "4"), ("Q1", "3"))),
    ("unit: +24 V on the old bus pin J1.16", "unit", lambda nl: move_node(nl, ("J1", "16"), ("Q1", "3"))),
    ("common: mounting hole H3 on 0 V instead of CHASSIS", "common", lambda nl: move_node(nl, ("H3", "1"), ("J3", "2"))),
    ("unit: RCH1 moved onto CHASSIS (pair shorted out)", "unit", lambda nl: move_node(nl, ("RCH1", "2"), ("H1", "1"))),
    ("common: 0 V connector pin J2.19 shorted to CHASSIS", "common", lambda nl: move_node(nl, ("J2", "19"), ("H1", "1"))),
    ("common POS: l bit 0 / r bit 0 swapped on J4 (pins 1<->11)", "common", lambda nl: swap_node(nl, "J4", "1", "11")),
    # 0003 K7 (bus B)
    ("common bus B: a2 hold-rail OR D805 fed from ZL (bus A) instead of ZL_B", "common",
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    if errs:
        print("FAIL structure:", errs[:5])
        return 1
    print("structure (0003 K7, clock bus B): CLOCK_B J5 = own CK_B/NCK_B/LOAD_B, unit bus B J6 = J2 pin layout with its own "
          "rails A2B_B Z2B_B A1B_B Z1B_B + LOAD_B (code lines and 0 V shared), 10 twin master coils parallel to the pL/pM masters")
    iso = bus_isolation_errors(common, unit)
    if iso:
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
